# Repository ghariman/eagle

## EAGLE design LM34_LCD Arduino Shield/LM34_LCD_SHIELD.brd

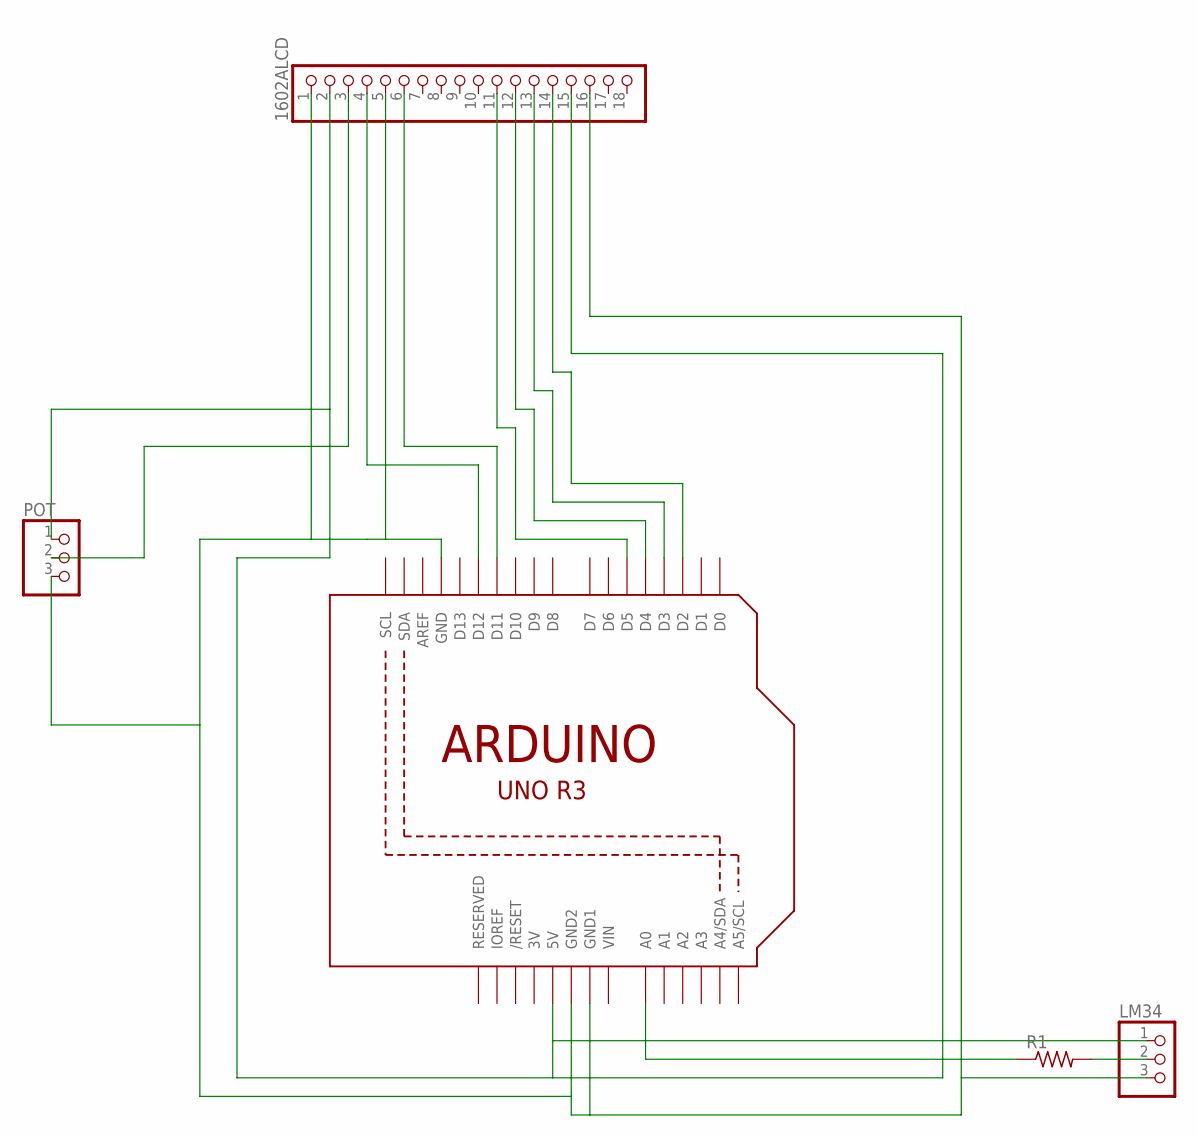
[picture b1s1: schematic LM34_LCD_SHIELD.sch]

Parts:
1602ALCD: PINHD-1X18; 1X18
LM34: PINHD-1X3CB; 1X03-CLEANBIG
POT: PINHD-1X3CB; 1X03-CLEANBIG
R1: R-US_0207/5V; 0207/5V
U1: ARDUINOR3-BPLACE

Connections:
3V: U1.3V
5V: 1602ALCD.2, 1602ALCD.15, LM34.1, POT.1, U1.5V
unnamed: 1602ALCD.4, U1.D12
unnamed: LM34.2, R1.2
unnamed: 1602ALCD.14, U1.D2
unnamed: 1602ALCD.6, U1.D11
unnamed: 1602ALCD.11, U1.D5
unnamed: 1602ALCD.12, U1.D4
unnamed: 1602ALCD.13, U1.D3
unnamed: R1.1, U1.A0
unnamed: 1602ALCD.3, POT.2
unnamed: 1602ALCD.1, 1602ALCD.5, 1602ALCD.16, LM34.3, POT.3, U1.GND, U1.GND1, U1.GND2
VIN: U1.VIN

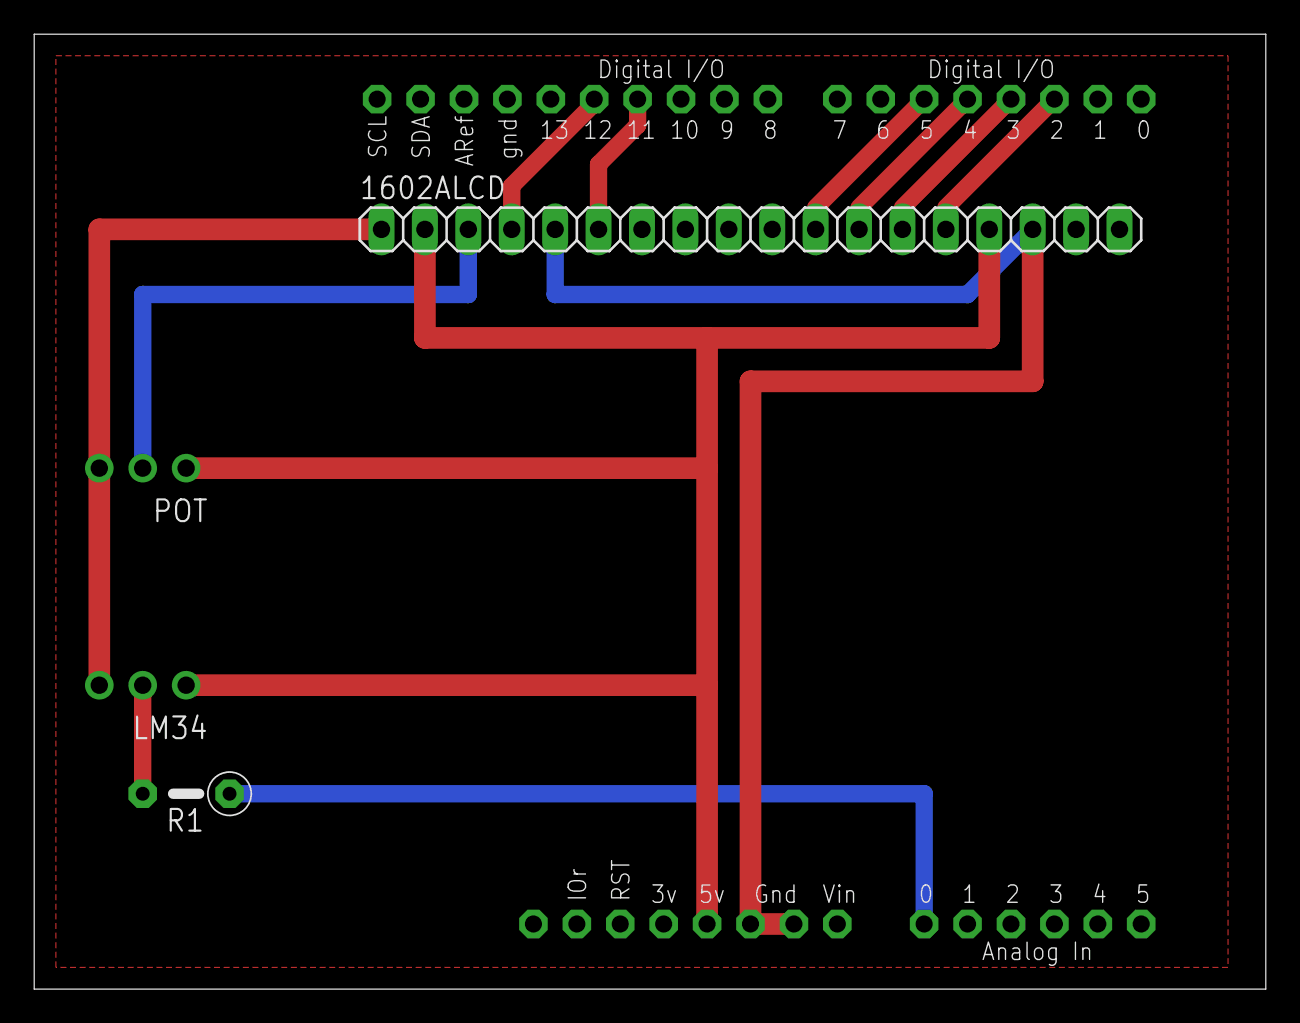
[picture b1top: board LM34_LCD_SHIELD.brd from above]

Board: 2 copper layers, 72.1 x 55.9 mm, 5 parts (0 on the bottom side), 11 nets.

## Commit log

2016-03-23 Added files via upload
